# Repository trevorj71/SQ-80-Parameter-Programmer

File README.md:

# PG-80 Crosswave Parameter Programmer for Ensoniq SQ-80 and Ensoniq ESQ1

This repo contains open source hardware and software for the Ensoniq SQ-80 and ESQ-1 hybrid synthesizers, which I have named the "PG-80". It allows you to program up to 63 parameters in your synthesis engine using the 32 knobs on the front panel. It also supports hidden waves if your synth is equipped with an OS that supports them on the front panel. It also features a MIDI merge feature so you can run an input from your MIDI interface through the programmer to the synth, inserting the programmer in-line so it doesn't add unnecessarily to your workflow or MIDI rats nest.

I'm still tweaking the firmware to improve the knob layout and I have a new housing version in progress to accomodate a larger OLED display, but the current design is debugged and functional.

A BOM will be forthcoming when I have a few minutes to add it.

# Housing

My vision for this unit was always been a sidecar that can sit next to the synth on a stand designed for a 76 key workstation and looks like an extension of the synth to the extent possible.  Likely, you could design a smaller housing for desktop, as mine is not necessarily designed
to minimize its footprint or print time. 

The 3D models for the prototype are will be published here in both Fusion 360 and STL formats.

## Prototype Version (Adafruit 326 and PCB Mounted MIDI Connections)

For my first build, I used PCB mounted MIDI connectors and a PCB that was optimized for production and shipping cost. This left me with limited space between the knob array and the back panel of the unit for an OLED, so I used an Adafruit 326 0.91mm display.  This was fine for prototyping but in practice in the studio it is really hard to read.  Otherwise the knob layout feels good and the overall geometry of the print meets the vision. 

I did have some slippage in my printer late in this job (which took 5 days) so there is a bit of a bondo job on this, but it works for a prototype.

## In Progress Updgraded Version (Adafruit ... and Panel Mounted MIDI Connecitons)

Build two will switch to a 2.42 inch Adafruit 2719 and panel mounted MIDI connections. Design for that enclosure is under way.

# Glitch Mode (Hidden Waveform) and Shift Switch

This momentary pushbutton switch, SW2, has two functions. 

A quick tap of this swtich enables glitch mode. This allows knobs 1-3 (oscillator waveforms) to transmit all 255 available parameters to the synth. If you have an OS for your synth that supports hidden waveforms, you will be able to scroll through all 255 paramteters. This only works with the modified OS versions that support hidden waves.

Pressing and holding this switch while also turning a knob makes it function as a shift key, letting you change the MIDI channel on your device or modify up to 63 parameters in your synthesis workflow. Failing to turn a knob while the switch is depressed reverts the programmer to Glitch Mode / Standard Mode.

# Arch Mode (SQ-80 / ESQ-1) Toggle

A panel mounted toggle switch, SW1, facilitates switching between the 32 wave ESQ-1 table and the 75 wave SQ-80 table. In standard mode, this aligns the values sent by the oscillator waveform knobs within the desired range for your model synth. In Glitch Mode, this is more a matter of the mask used for the OLED on parameters 33-75, since all 255 parameters can be transmitted to the synth.

# Potentiometer Layout

Currently, the programmer has been laid out with 32 Potentiometers. You can access up to 63 parameters plus MIDI channel by pressing and holding the Hidden Waveforms button like a shift key.  

The knob layout as of version 1.5 is as follows:

### GLITCH BUTTON IN THE UP POSITION - NOT PRESSED

| Oscillator 1 | Oscillator 2 | Oscillator 3 | DCA-Filter | MOD 1 | MOD 2 | ENV 1-3 | ENV 2-4 
| :---: | :---: | :---: | :---: | :---: | :---: | :---: | :---: |
| WAVEFORM | WAVEFORM | WAVEFORM | DCA1 VOL | LFO1 WAVE | LFO2 FREQ | ENV1 ATK | ENV2 ATK 
| OSC1 FINE | OSC2 FINE | OSC3 FINE | DCA2 VOL | LFO1 FREQ | LFO3 WAVE | ENV1 DEC | ENV2 DEC 
| OSC1 COAR | OSC2 COAR | OSC3 COAR | DCA3 VOL | LFO1 DELY | LFO3 FREQ | ENV1 REL | ENV2 REL
| OSC1 OCT | OSC2 OCT | OSC3 OCT | ENV4 VOL | LFO2 WAVE | LFO3 DELY | ENV1 SUS | ENV2 SUS 

### GLITCH BUTTON HELD DOWN WHILE TURNING

| Oscillator 1 | Oscillator 2 | Oscillator 3 | DCA-Filter | MOD 1 | MOD 2 | ENV 1-3 | ENV 2-4 
| :---: | :---: | :---: | :---: | :---: | :---: | :---: | :---: |
| MOD1 SRC | MOD1 SRC | MOD1 SRC | FILT CUT | LFO1 L1 | LFO2 LS | ENV3 ATK | ENV4 ATK 
| MOD1 LEV | MOD1 LEV | MOD1 LEV | FILT RES | LFO1 L2 | LFO3 L1` | ENV3 DEC | ENV4 DEC 
| MOD2 SRC | MOD2 SRC | MOD2 SRC | FILT MOD3 | LFO2 DELY | LFO3 L2 | ENV3 REL | ENV4 REL
| MOD2 LEV | MOD2 LEV | MOD2 LEV | VOICE PAN | LFO2 L1 | MIDI CHAN | ENV3 SUS | ENV4 SUS

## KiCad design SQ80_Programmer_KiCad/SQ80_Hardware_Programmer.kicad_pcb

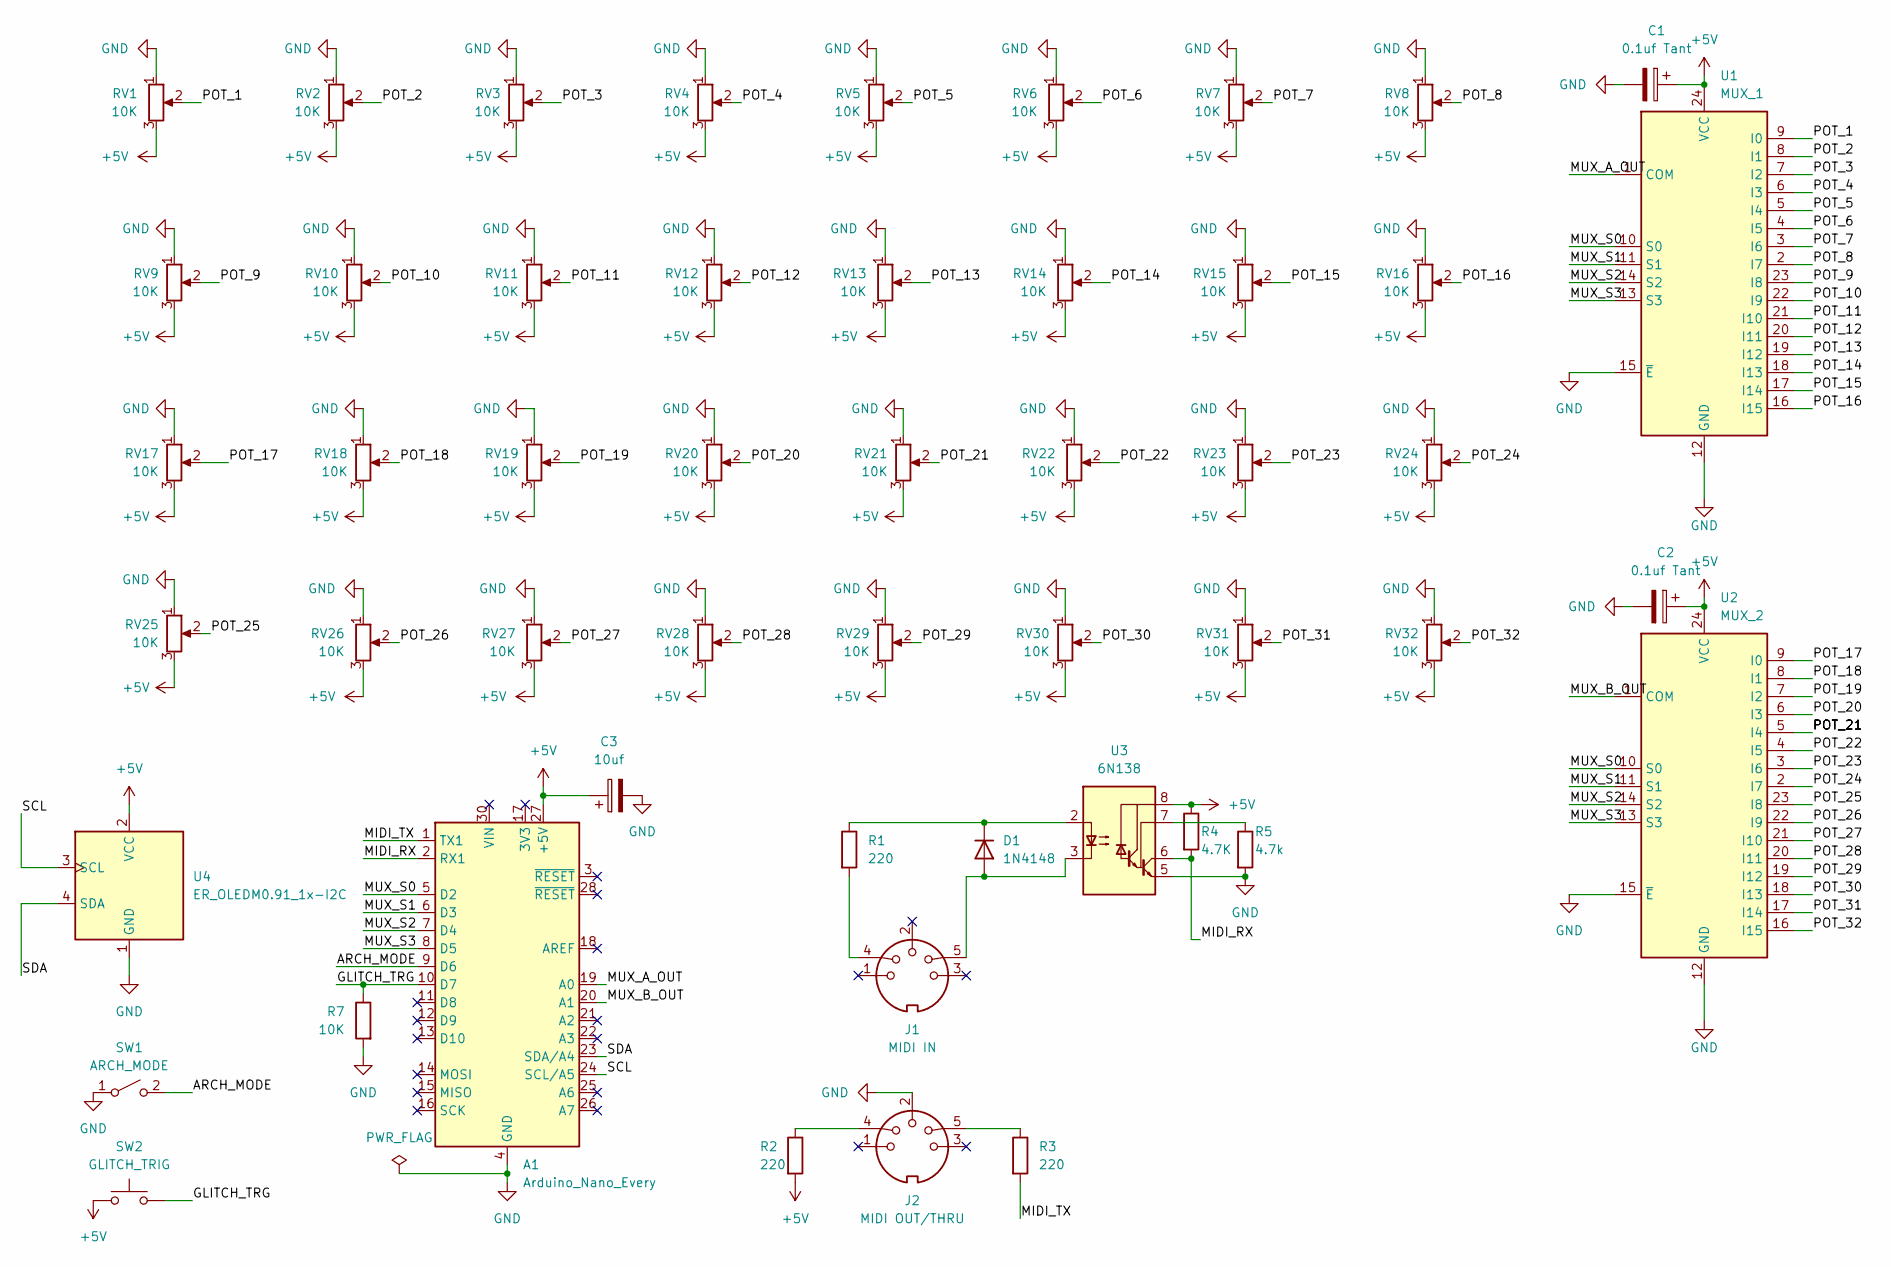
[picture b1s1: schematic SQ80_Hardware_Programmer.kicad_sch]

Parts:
A1: Arduino_Nano_Every; Arduino_Nano
C1, C2: 0.1uf Tant; CP_Radial_Tantal_D5.0mm_P2.50mm
C3: 10uf; CP_Radial_D5.0mm_P2.00mm
D1: 1N4148; D_DO-35_SOD27_P7.62mm_Horizontal
J1: MIDI IN; CONN5_SDS-50J_CUD
J2: MIDI OUT/THRU; CONN5_SDS-50J_CUD
R1, R2, R3: 220; R_Axial_DIN0207_L6.3mm_D2.5mm_P15.24mm_Horizontal
R4: 4.7K; R_Axial_DIN0207_L6.3mm_D2.5mm_P15.24mm_Horizontal
R5: 4.7k; R_Axial_DIN0207_L6.3mm_D2.5mm_P15.24mm_Horizontal
R7: 10K; R_Axial_DIN0207_L6.3mm_D2.5mm_P15.24mm_Horizontal
RV1, RV2, RV3, RV4, RV5, RV6, RV7, RV8, RV9, RV10, RV11, RV12, RV13, RV14, RV15, RV16, RV17, RV18, RV19, RV20, RV21, RV22, RV23, RV24, RV25, RV26, RV27, RV28, RV29, RV30, RV31, RV32: 10K; Potentiometer_Bourns_PTV09A-1_Single_Vertical
SW1: ARCH_MODE; PinHeader_1x03_P2.54mm_Vertical
SW2: GLITCH_TRIG; SW_PUSH_6mm
U1: MUX_1; SOIC-24W_7.5x15.4mm_P1.27mm
U2: MUX_2; SOIC-24W_7.5x15.4mm_P1.27mm
U3: 6N138; DIP-8_W7.62mm
U4: ER_OLEDM0.91_1x-I2C

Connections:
+5V: A1.27 (+5V), C1.1, C2.1, C3.1, R2.2, R4.1, RV1.3, RV2.3, RV3.3, RV4.3, RV5.3, RV6.3, RV7.3, RV8.3, RV9.3, RV10.3, RV11.3, RV12.3, RV13.3, RV14.3, RV15.3, RV16.3, RV17.3, RV18.3, RV19.3, RV20.3, RV21.3, RV22.3, RV23.3, RV24.3, RV25.3, RV26.3, RV27.3, RV28.3, RV29.3, RV30.3, RV31.3, RV32.3, SW2.1, U1.24 (VCC), U2.24 (VCC), U3.8 (VCC), U4.2 (VCC)
/ARCH_MODE: A1.9 (D6), SW1.2 (B)
/GLITCH_TRG: A1.10 (D7), R7.1, SW2.2
/MIDI_RX: A1.2 (RX1), R4.2, U3.6 (VO2)
/MIDI_TX: A1.1 (TX1), R3.2
/MUX_A_OUT: A1.19 (A0), U1.1 (COM)
/MUX_B_OUT: A1.20 (A1), U2.1 (COM)
/MUX_S0: A1.5 (D2), U1.10 (S0), U2.10 (S0)
/MUX_S1: A1.6 (D3), U1.11 (S1), U2.11 (S1)
/MUX_S2: A1.7 (D4), U1.14 (S2), U2.14 (S2)
/MUX_S3: A1.8 (D5), U1.13 (S3), U2.13 (S3)
/POT_1: RV1.2, U1.9 (I0)
/POT_2: RV2.2, U1.8 (I1)
/POT_3: RV3.2, U1.7 (I2)
/POT_4: RV4.2, U1.6 (I3)
/POT_5: RV5.2, U1.5 (I4)
/POT_6: RV6.2, U1.4 (I5)
/POT_7: RV7.2, U1.3 (I6)
/POT_8: RV8.2, U1.2 (I7)
/POT_9: RV9.2, U1.23 (I8)
/POT_10: RV10.2, U1.22 (I9)
/POT_11: RV11.2, U1.21 (I10)
/POT_12: RV12.2, U1.20 (I11)
/POT_13: RV13.2, U1.19 (I12)
/POT_14: RV14.2, U1.18 (I13)
/POT_15: RV15.2, U1.17 (I14)
/POT_16: RV16.2, U1.16 (I15)
/POT_17: RV17.2, U2.9 (I0)
/POT_18: RV18.2, U2.8 (I1)
/POT_19: RV19.2, U2.7 (I2)
/POT_20: RV20.2, U2.6 (I3)
/POT_21: RV21.2, U2.5 (I4)
/POT_22: RV22.2, U2.4 (I5)
/POT_23: RV23.2, U2.3 (I6)
/POT_24: RV24.2, U2.2 (I7)
/POT_25: RV25.2, U2.23 (I8)
/POT_26: RV26.2, U2.22 (I9)
/POT_27: RV27.2, U2.21 (I10)
/POT_28: RV28.2, U2.20 (I11)
/POT_29: RV29.2, U2.19 (I12)
/POT_30: RV30.2, U2.18 (I13)
/POT_31: RV31.2, U2.17 (I14)
/POT_32: RV32.2, U2.16 (I15)
/SCL: A1.24 (SCL/A5), U4.3 (SCL)
/SDA: A1.23 (SDA/A4), U4.4 (SDA)
GND: A1.4 (GND), A1.29 (GND), C1.2, C2.2, C3.2, J2.2, R5.2, R7.2, RV1.1, RV2.1, RV3.1, RV4.1, RV5.1, RV6.1, RV7.1, RV8.1, RV9.1, RV10.1, RV11.1, RV12.1, RV13.1, RV14.1, RV15.1, RV16.1, RV17.1, RV18.1, RV19.1, RV20.1, RV21.1, RV22.1, RV23.1, RV24.1, RV25.1, RV26.1, RV27.1, RV28.1, RV29.1, RV30.1, RV31.1, RV32.1, SW1.1 (A), U1.12 (GND), U1.15 (~E), U2.12 (GND), U2.15 (~E), U3.5 (GND), U4.1 (GND)
unnamed: D1.2 (A), J1.5, U3.3 (C2)
unnamed: D1.1 (K), R1.1, U3.2 (C1)
unnamed: J1.4, R1.2
unnamed: J2.4, R2.1
unnamed: J2.5, R3.1
unnamed: R5.1, U3.7 (VO1)

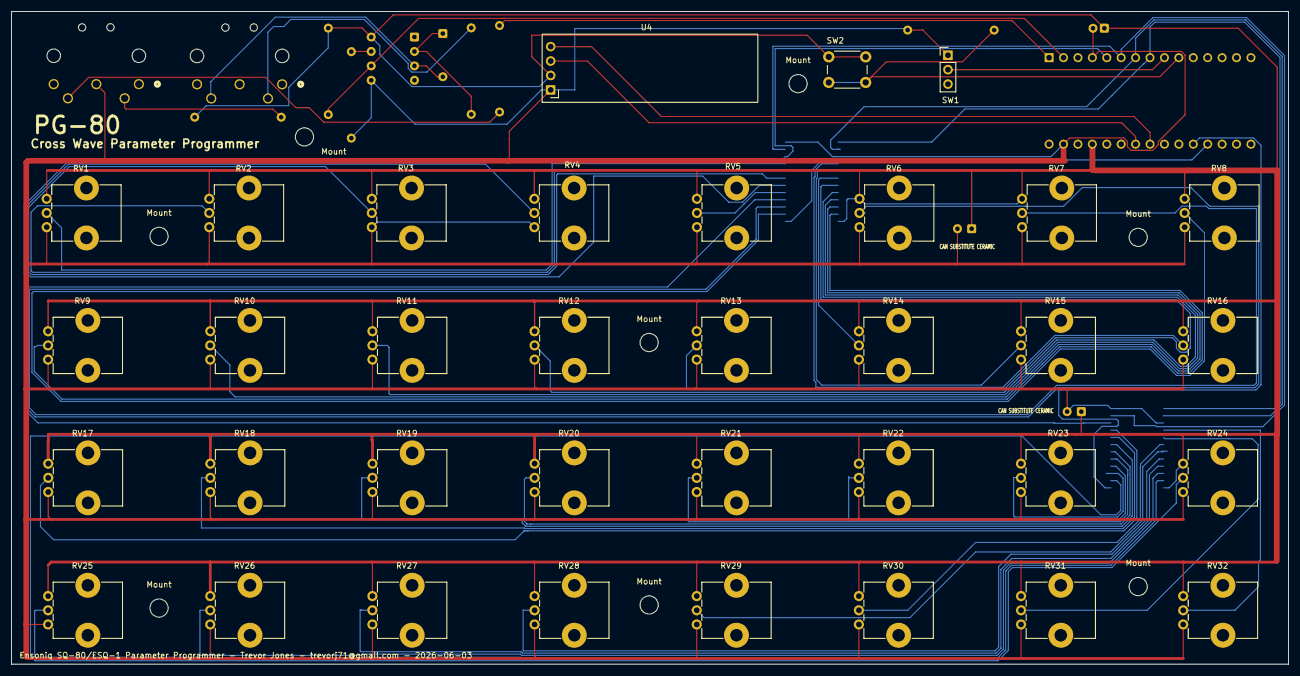
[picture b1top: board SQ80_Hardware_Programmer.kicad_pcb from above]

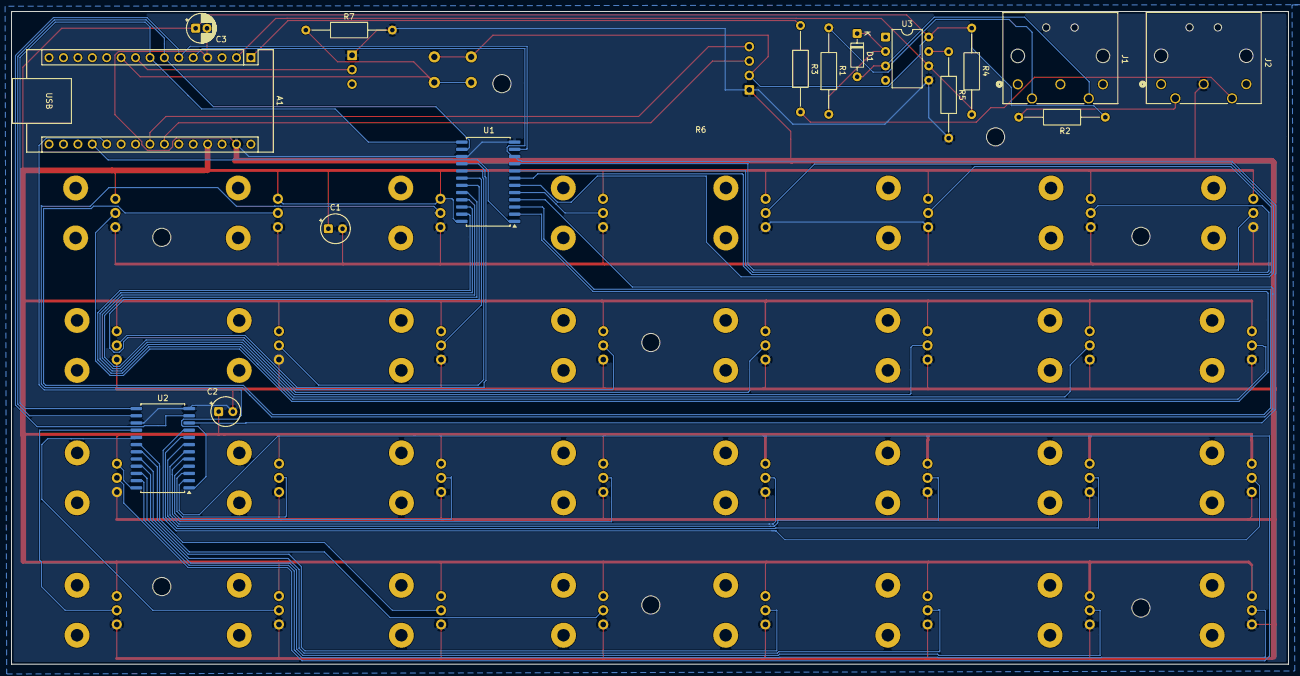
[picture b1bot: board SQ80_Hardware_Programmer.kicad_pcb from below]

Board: 2 copper layers, 225.0 x 115.0 mm, 59 parts (16 on the bottom side), 52 nets.

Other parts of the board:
Mount: MountingHole_3.2mm_M3
Mount#2, Mount#3, Mount#4, Mount#5, Mount#6, Mount#7, Mount#8: MountingHole_3.2mm_M3

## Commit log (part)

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2026-06-30 Create KiCad_Project
2026-06-30 Initial Upload of KiCad files and Code
2026-06-30 File move
2026-06-30 Work in Progress README
2026-06-30 Moving README to root
